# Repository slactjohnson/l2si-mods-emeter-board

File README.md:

# l2si-mods-emeter-board
Repository for the L2SI Laser MODS system energy meter diagnostic PCB.

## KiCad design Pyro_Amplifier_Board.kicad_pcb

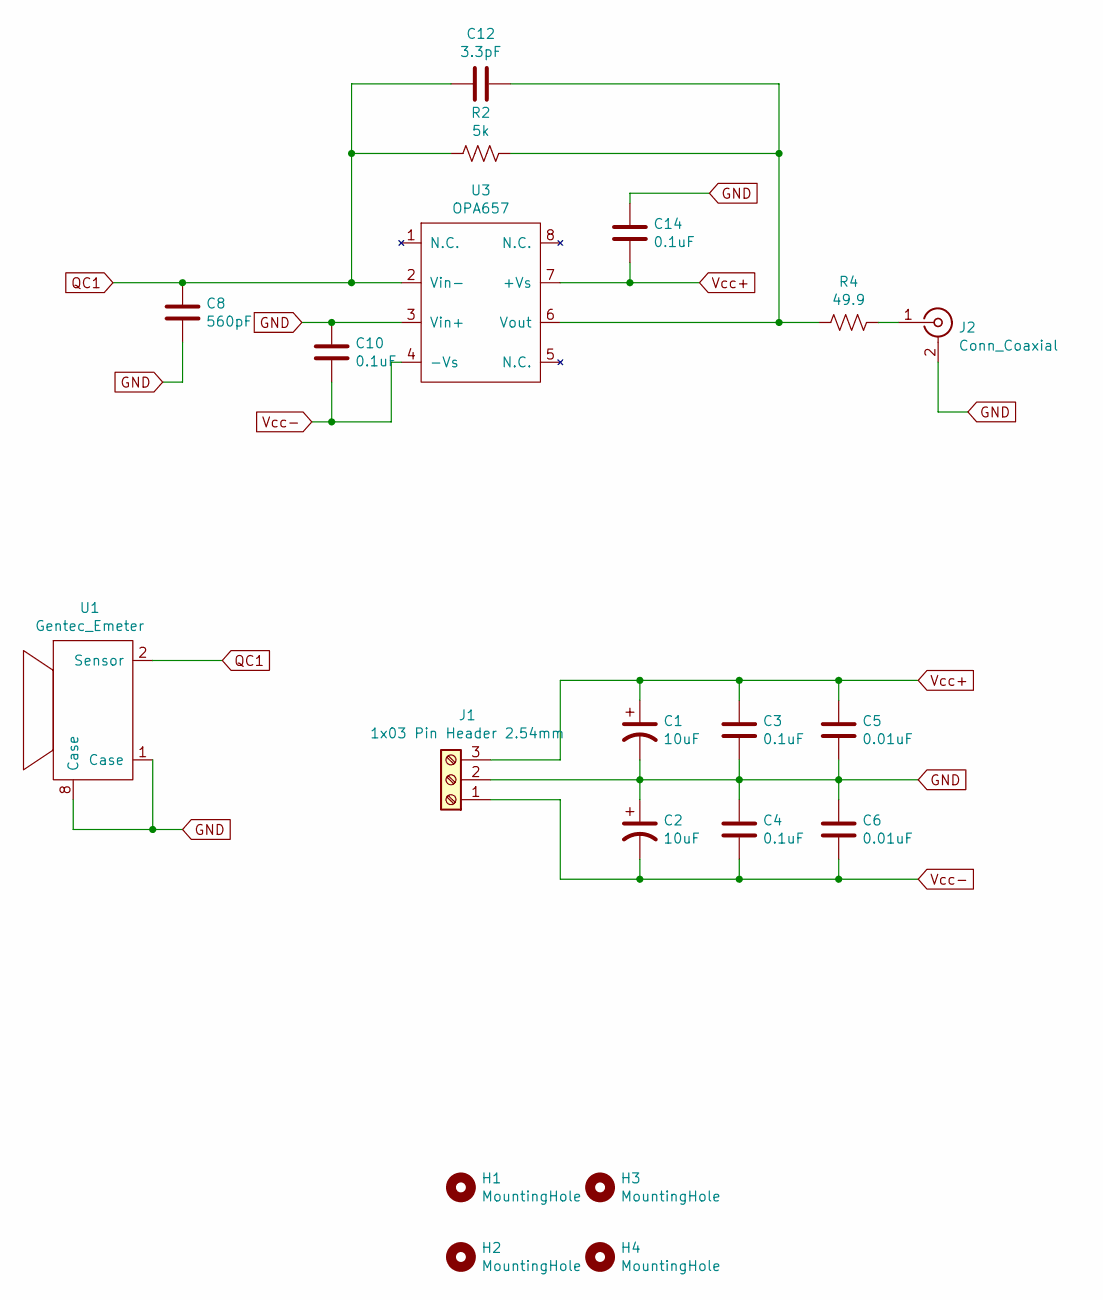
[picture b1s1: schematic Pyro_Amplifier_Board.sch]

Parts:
C1, C2: 10uF; CP_Radial_D10.0mm_P5.00mm
C3, C4, C10, C14: 0.1uF; C_0805_2012Metric_Pad1.15x1.40mm_HandSolder
C5, C6: 0.01uF; C_0805_2012Metric_Pad1.15x1.40mm_HandSolder
C8: 560pF; C_0805_2012Metric_Pad1.15x1.40mm_HandSolder
C12: 3.3pF; C_0805_2012Metric_Pad1.15x1.40mm_HandSolder
H1, H2, H3, H4: MountingHole; ThorLabs_6mm_CageSystem_MountHole
J1: 1x03 Pin Header 2.54mm; PinHeader_1x03_P2.54mm_Horizontal
J2: Conn_Coaxial; SMA_Amphenol_132134-11_Vertical
R2: 5k; R_0805_2012Metric_Pad1.15x1.40mm_HandSolder
R4: 49.9; R_0805_2012Metric_Pad1.15x1.40mm_HandSolder
U1: Gentec_Emeter; TO-8_Can_8_Leads
U3: OPA657; SOIC-8_3.9x4.9mm_P1.27mm

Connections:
GND: C1.2, C2.1, C3.1, C4.2, C5.1, C6.2, C8.2, C10.1, C14.2, J1.2, J2.2 (Ext), U1.1 (Case), U1.8 (Case), U3.3 (Vin+)
unnamed: C12.1, R2.1, R4.2, U3.6 (Vout)
unnamed: J2.1 (In), R4.1
QC1: C8.1, C12.2, R2.2, U1.2 (Sensor), U3.2 (Vin-)
Vcc+: C1.1, C3.2, C5.2, C14.1, J1.3, U3.7 (+Vs)
Vcc-: C2.2, C4.1, C6.1, C10.2, J1.1, U3.4 (-Vs)

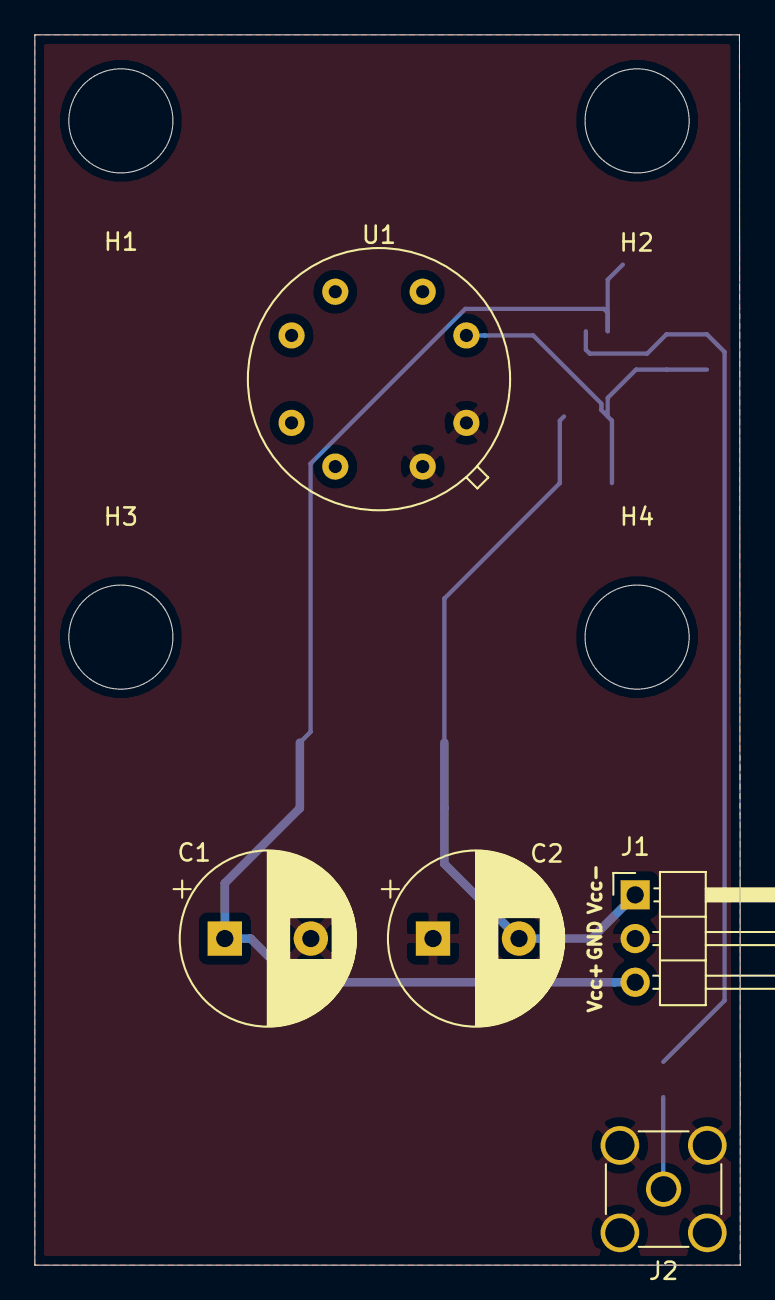
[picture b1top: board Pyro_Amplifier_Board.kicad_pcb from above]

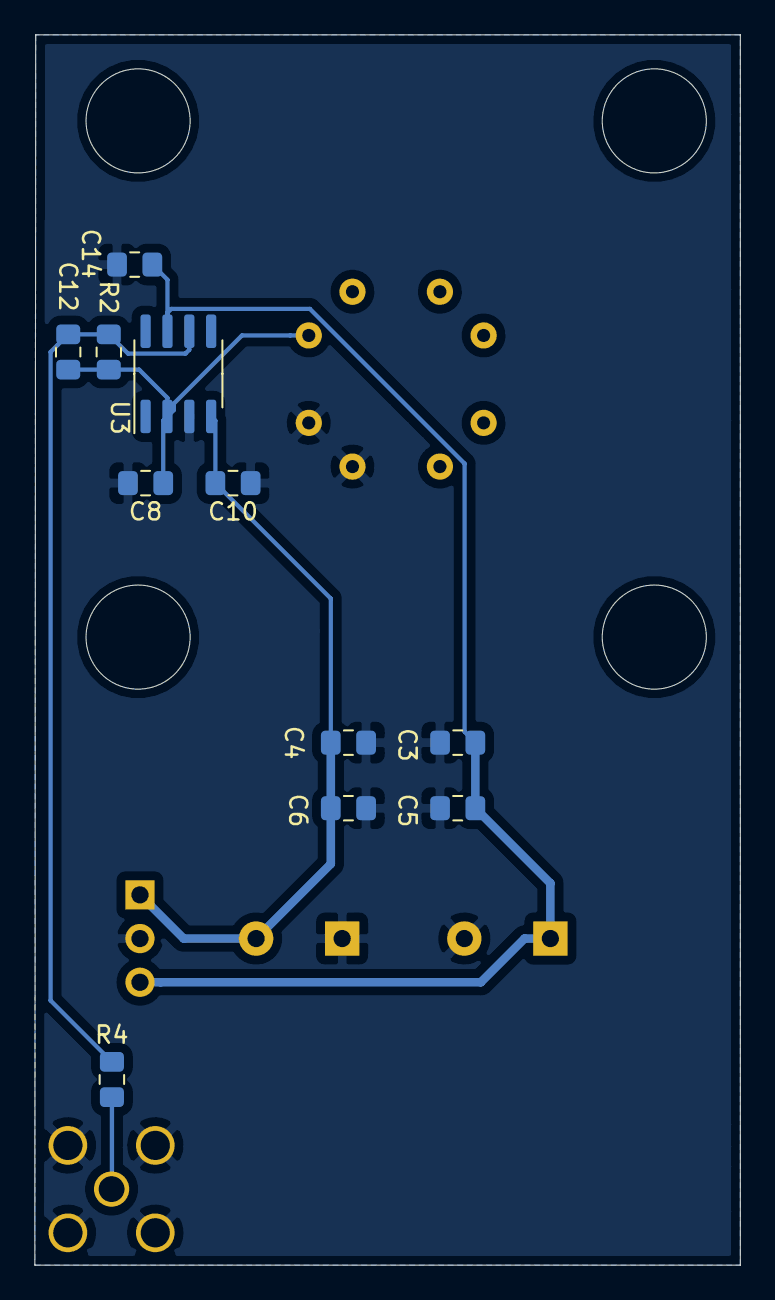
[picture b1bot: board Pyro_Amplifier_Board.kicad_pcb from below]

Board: 2 copper layers, 41.0 x 71.5 mm, 20 parts (11 on the bottom side), 6 nets.

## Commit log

2020-09-13 Initial commit of design files.
